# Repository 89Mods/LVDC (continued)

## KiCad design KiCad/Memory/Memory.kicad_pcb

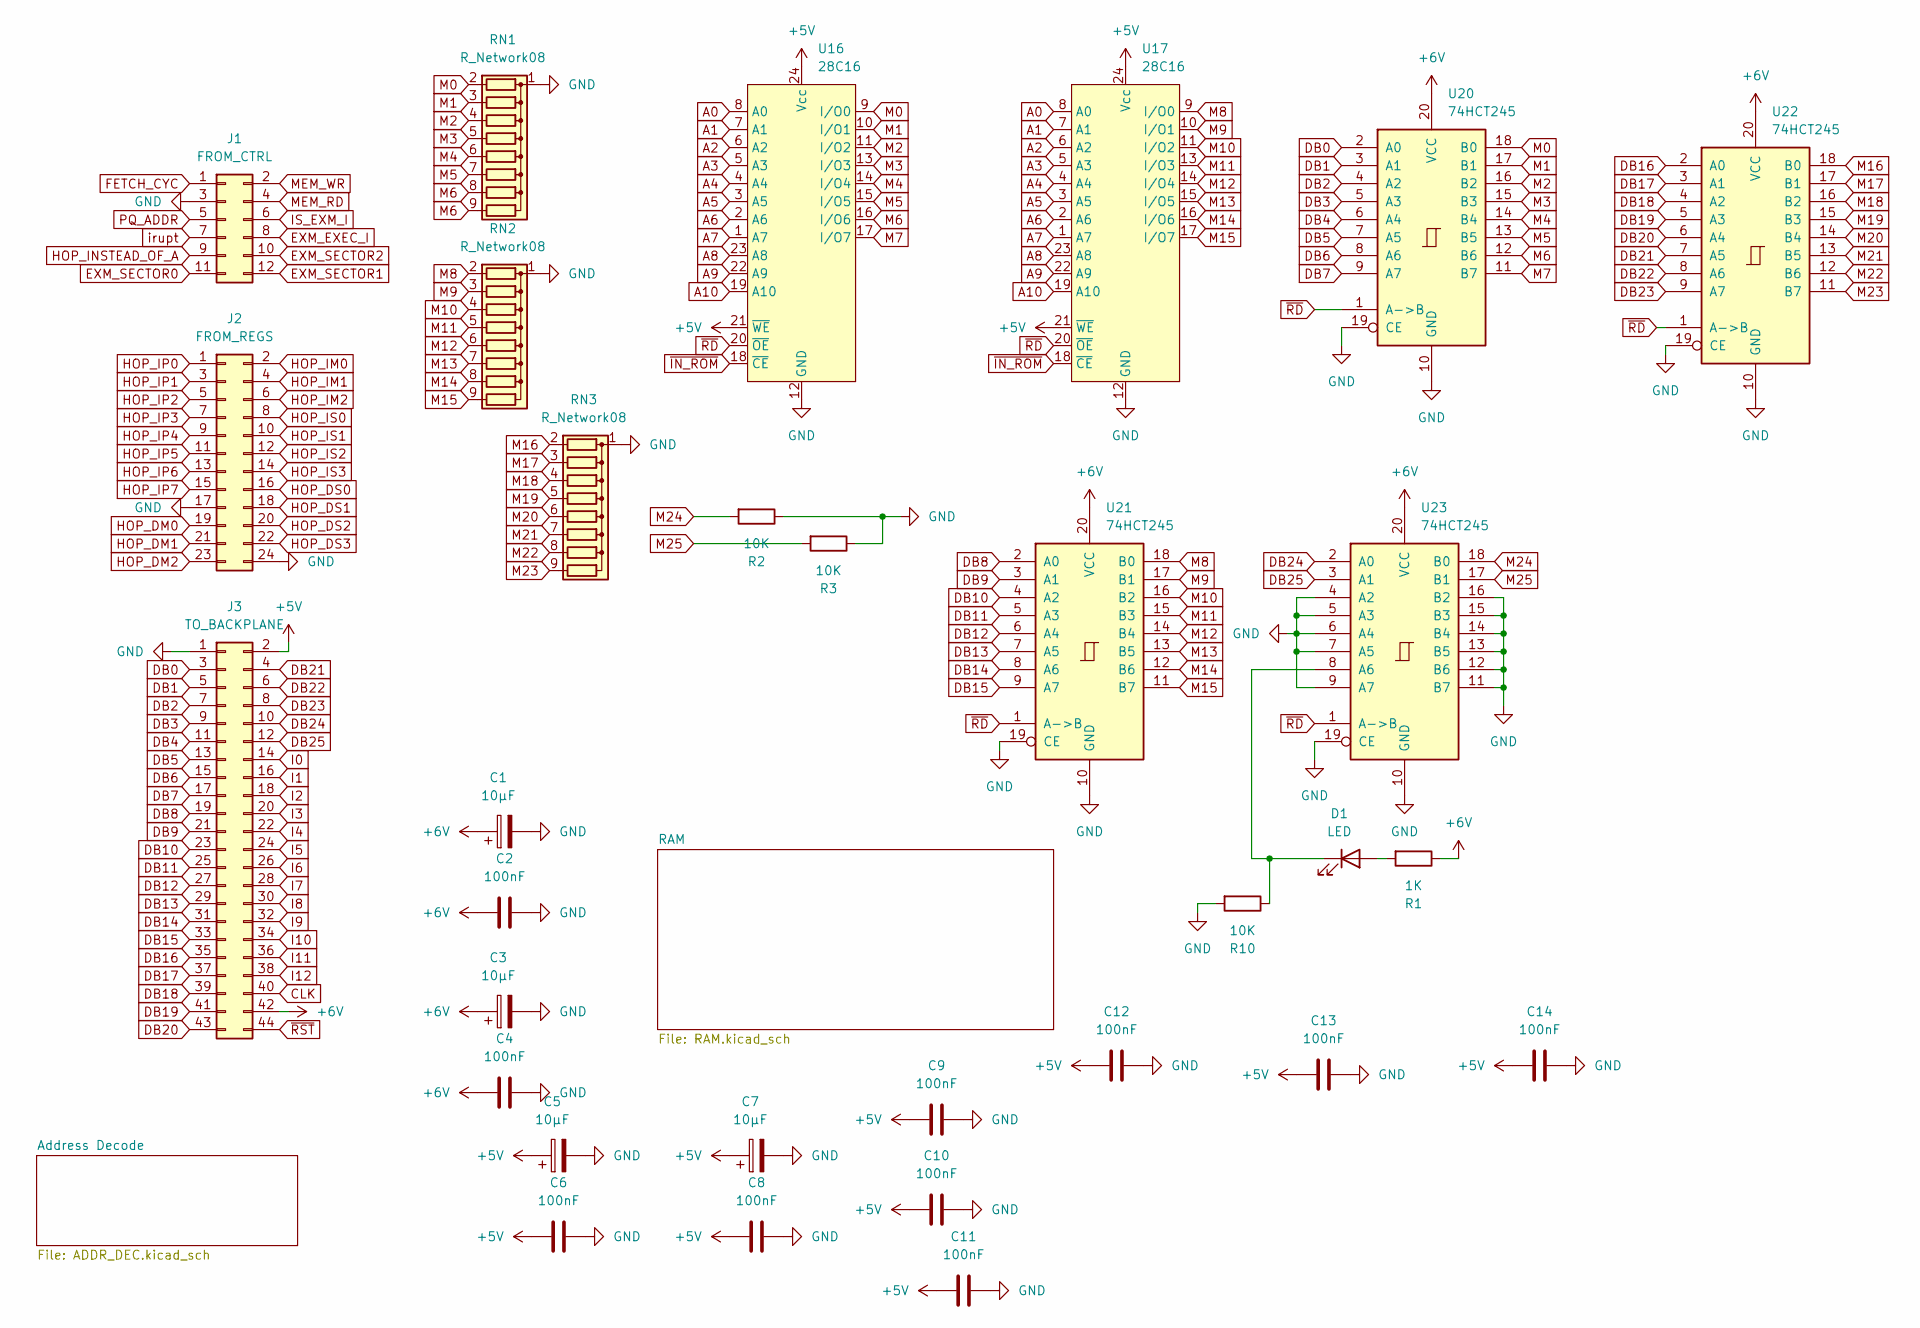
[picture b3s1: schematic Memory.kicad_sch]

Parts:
C1, C3, C5, C7: 10µF; CP_Radial_D4.0mm_P2.00mm
C2, C4, C6, C8, C9, C10, C11, C12, C13, C14: 100nF; C_0805_2012Metric_Pad1.18x1.45mm_HandSolder
D1: LED; LED_1206_3216Metric_Pad1.42x1.75mm_HandSolder
J1: FROM_CTRL; PinHeader_2x06_P2.54mm_Vertical
J2: FROM_REGS; PinHeader_2x12_P2.54mm_Vertical
J3: TO_BACKPLANE; PinHeader_2x22_P2.54mm_Vertical
R1: 1K; R_1206_3216Metric_Pad1.30x1.75mm_HandSolder
R2, R3, R10: 10K; R_1206_3216Metric_Pad1.30x1.75mm_HandSolder
RN1, RN2, RN3: R_Network08; R_Array_SIP9
U16, U17: 28C16; DIP-24_W15.24mm
U20, U21, U22, U23: 74HCT245; SO-20_12.8x7.5mm_P1.27mm

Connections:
+5V: C5.1, C6.1, C7.1, C8.1, C9.1, C10.1, C11.1, C12.1, C13.1, C14.1, J3.2, U16.21 (~WE), U16.24 (Vcc), U17.21 (~WE), U17.24 (Vcc); also elsewhere on the board
+6V: C1.1, C2.1, C3.1, C4.1, J3.42, R1.1, U20.20 (VCC), U21.20 (VCC), U22.20 (VCC), U23.20 (VCC)
A0: U16.8 (A0), U17.8 (A0); also elsewhere on the board
A1: U16.7 (A1), U17.7 (A1); also elsewhere on the board
A2: U16.6 (A2), U17.6 (A2); also elsewhere on the board
A3: U16.5 (A3), U17.5 (A3); also elsewhere on the board
A4: U16.4 (A4), U17.4 (A4); also elsewhere on the board
A5: U16.3 (A5), U17.3 (A5); also elsewhere on the board
A6: U16.2 (A6), U17.2 (A6); also elsewhere on the board
A7: U16.1 (A7), U17.1 (A7); also elsewhere on the board
A8: U16.23 (A8), U17.23 (A8); also elsewhere on the board
A9: U16.22 (A9), U17.22 (A9); also elsewhere on the board
A10: U16.19 (A10), U17.19 (A10); also elsewhere on the board
CLK: J3.40
DB0: J3.3, U20.2 (A0)
DB1: J3.5, U20.3 (A1)
DB2: J3.7, U20.4 (A2)
DB3: J3.9, U20.5 (A3)
DB4: J3.11, U20.6 (A4)
DB5: J3.13, U20.7 (A5)
DB6: J3.15, U20.8 (A6)
DB7: J3.17, U20.9 (A7)
DB8: J3.19, U21.2 (A0)
DB9: J3.21, U21.3 (A1)
DB10: J3.23, U21.4 (A2)
DB11: J3.25, U21.5 (A3)
DB12: J3.27, U21.6 (A4)
DB13: J3.29, U21.7 (A5)
DB14: J3.31, U21.8 (A6)
DB15: J3.33, U21.9 (A7)
DB16: J3.35, U22.2 (A0)
DB17: J3.37, U22.3 (A1)
DB18: J3.39, U22.4 (A2)
DB19: J3.41, U22.5 (A3)
DB20: J3.43, U22.6 (A4)
DB21: J3.4, U22.7 (A5)
DB22: J3.6, U22.8 (A6)
DB23: J3.8, U22.9 (A7)
DB24: J3.10, U23.2 (A0)
DB25: J3.12, U23.3 (A1)
EXM_EXEC_I: J1.8; also elsewhere on the board
EXM_SECTOR0: J1.11; also elsewhere on the board
EXM_SECTOR1: J1.12; also elsewhere on the board
EXM_SECTOR2: J1.10; also elsewhere on the board
FETCH_CYC: J1.1; also elsewhere on the board
GND: C1.2, C2.2, C3.2, C4.2, C5.2, C6.2, C7.2, C8.2, C9.2, C10.2, C11.2, C12.2, C13.2, C14.2, J1.3, J2.17, J2.24, J3.1, R2.1, R3.1, R10.2, RN1.1 (common), RN2.1 (common), RN3.1 (common), U16.12 (GND), U17.12 (GND), U20.10 (GND), U20.19 (CE), U21.10 (GND), U21.19 (CE), U22.10 (GND), U22.19 (CE), U23.4 (A2), U23.5 (A3), U23.6 (A4), U23.7 (A5), U23.9 (A7), U23.10 (GND), U23.11 (B7), U23.12 (B6), U23.13 (B5), U23.14 (B4), U23.15 (B3), U23.16 (B2), U23.19 (CE); also elsewhere on the board
HOP_DM0: J2.19; also elsewhere on the board
HOP_DM1: J2.21; also elsewhere on the board
HOP_DM2: J2.23; also elsewhere on the board
HOP_DS0: J2.16; also elsewhere on the board
HOP_DS1: J2.18; also elsewhere on the board
HOP_DS2: J2.20; also elsewhere on the board
HOP_DS3: J2.22; also elsewhere on the board
HOP_IM0: J2.2; also elsewhere on the board
HOP_IM1: J2.4; also elsewhere on the board
HOP_IM2: J2.6; also elsewhere on the board
HOP_INSTEAD_OF_A: J1.9; also elsewhere on the board
HOP_IP0: J2.1; also elsewhere on the board
HOP_IP1: J2.3; also elsewhere on the board
HOP_IP2: J2.5; also elsewhere on the board
HOP_IP3: J2.7; also elsewhere on the board
HOP_IP4: J2.9; also elsewhere on the board
HOP_IP5: J2.11; also elsewhere on the board
HOP_IP6: J2.13; also elsewhere on the board
HOP_IP7: J2.15; also elsewhere on the board
HOP_IS0: J2.8; also elsewhere on the board
HOP_IS1: J2.10; also elsewhere on the board
HOP_IS2: J2.12; also elsewhere on the board
HOP_IS3: J2.14; also elsewhere on the board
I0: J3.14
I1: J3.16
I2: J3.18
I3: J3.20
I4: J3.22; also elsewhere on the board
I5: J3.24; also elsewhere on the board
I6: J3.26; also elsewhere on the board
I7: J3.28; also elsewhere on the board
I8: J3.30; also elsewhere on the board
I9: J3.32; also elsewhere on the board
I10: J3.34; also elsewhere on the board
I11: J3.36; also elsewhere on the board
I12: J3.38; also elsewhere on the board
IS_EXM_I: J1.6; also elsewhere on the board
M0: RN1.2 (R1), U16.9 (I/O0), U20.18 (B0); also elsewhere on the board
M1: RN1.3 (R2), U16.10 (I/O1), U20.17 (B1); also elsewhere on the board
M2: RN1.4 (R3), U16.11 (I/O2), U20.16 (B2); also elsewhere on the board
M3: RN1.5 (R4), U16.13 (I/O3), U20.15 (B3); also elsewhere on the board
M4: RN1.6 (R5), U16.14 (I/O4), U20.14 (B4); also elsewhere on the board
M5: RN1.7 (R6), U16.15 (I/O5), U20.13 (B5); also elsewhere on the board
M6: RN1.8 (R7), RN1.9 (R8), U16.16 (I/O6), U20.12 (B6); also elsewhere on the board
M7: U16.17 (I/O7), U20.11 (B7); also elsewhere on the board
M8: RN2.2 (R1), U17.9 (I/O0), U21.18 (B0); also elsewhere on the board
M9: RN2.3 (R2), U17.10 (I/O1), U21.17 (B1); also elsewhere on the board
M10: RN2.4 (R3), U17.11 (I/O2), U21.16 (B2); also elsewhere on the board
M11: RN2.5 (R4), U17.13 (I/O3), U21.15 (B3); also elsewhere on the board
M12: RN2.6 (R5), U17.14 (I/O4), U21.14 (B4); also elsewhere on the board
M13: RN2.7 (R6), U17.15 (I/O5), U21.13 (B5); also elsewhere on the board
M14: RN2.8 (R7), U17.16 (I/O6), U21.12 (B6); also elsewhere on the board
M15: RN2.9 (R8), U17.17 (I/O7), U21.11 (B7); also elsewhere on the board
M16: RN3.2 (R1), U22.18 (B0); also elsewhere on the board
M17: RN3.3 (R2), U22.17 (B1); also elsewhere on the board
M18: RN3.4 (R3), U22.16 (B2); also elsewhere on the board
M19: RN3.5 (R4), U22.15 (B3); also elsewhere on the board
M20: RN3.6 (R5), U22.14 (B4); also elsewhere on the board
M21: RN3.7 (R6), U22.13 (B5); also elsewhere on the board
M22: RN3.8 (R7), U22.12 (B6); also elsewhere on the board
M23: RN3.9 (R8), U22.11 (B7); also elsewhere on the board
M24: R2.2, U23.18 (B0); also elsewhere on the board
M25: R3.2, U23.17 (B1); also elsewhere on the board
MEM_RD: J1.4; also elsewhere on the board
MEM_WR: J1.2; also elsewhere on the board
unnamed: D1.2 (A), R1.2
unnamed: D1.1 (K), R10.1, U23.8 (A6)
PQ_ADDR: J1.5; also elsewhere on the board
irupt: J1.7; also elsewhere on the board
~IN_ROM: U16.18 (~CE), U17.18 (~CE); also elsewhere on the board
~RD: U16.20 (~OE), U17.20 (~OE), U20.1 (A->B), U21.1 (A->B), U22.1 (A->B), U23.1 (A->B); also elsewhere on the board
~RST: J3.44

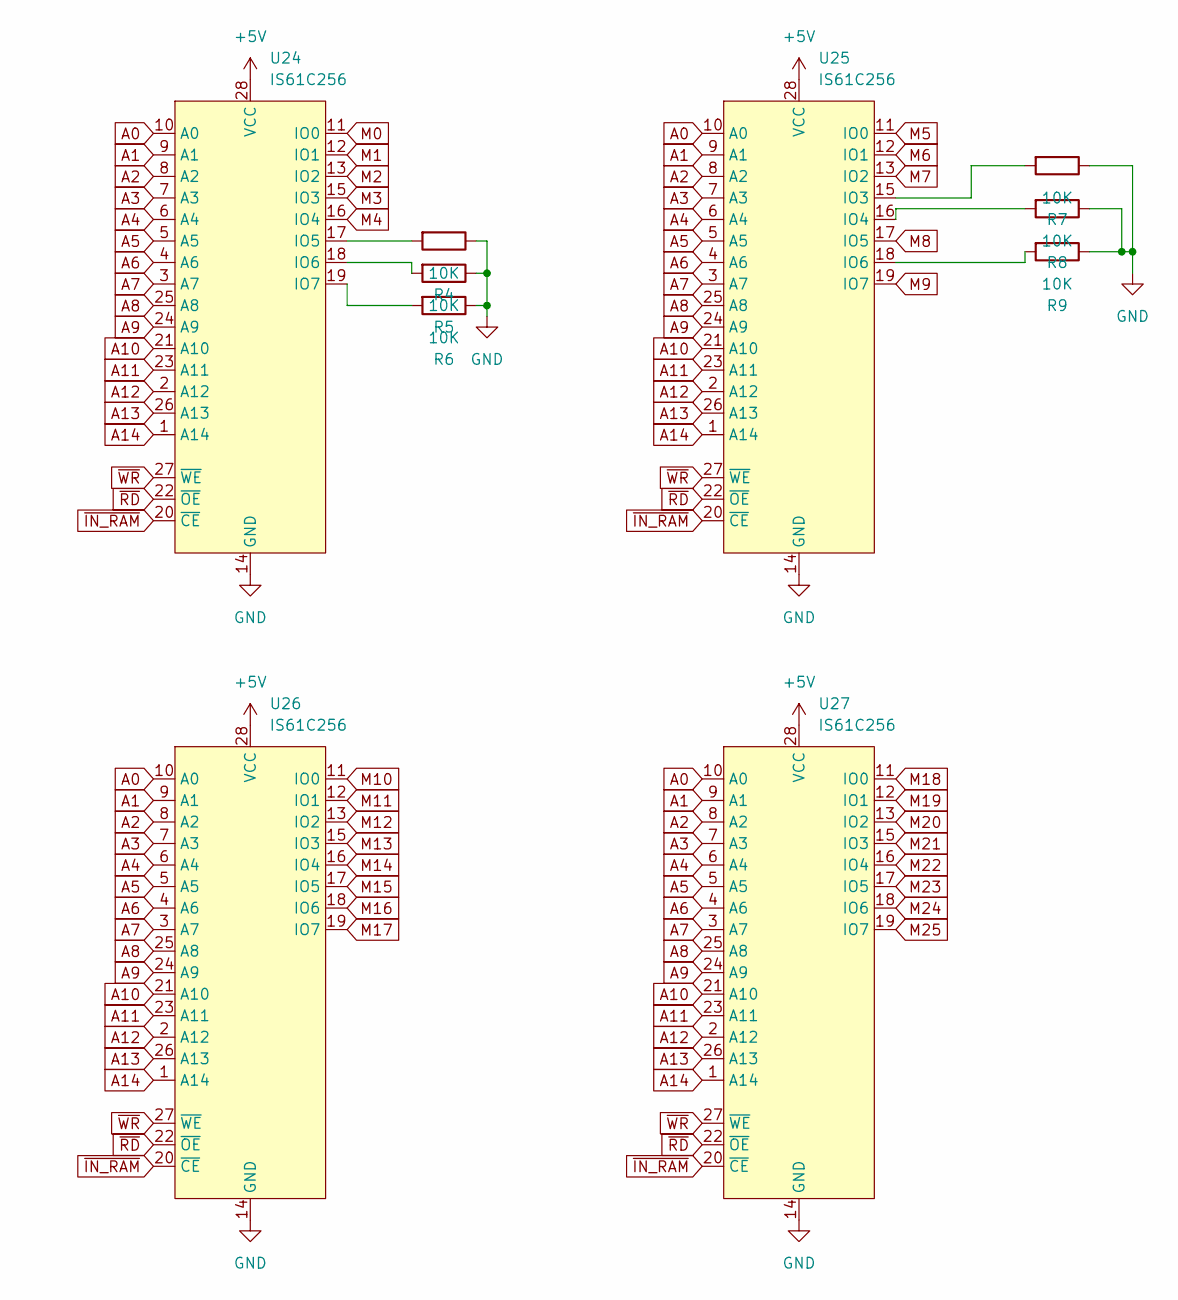
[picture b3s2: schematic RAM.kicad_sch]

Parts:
R4, R5, R6, R7, R8, R9: 10K; R_1206_3216Metric_Pad1.30x1.75mm_HandSolder
U24, U25, U26, U27: IS61C256; DIP-28_W7.62mm

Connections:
+5V: U24.28 (VCC), U25.28 (VCC), U26.28 (VCC), U27.28 (VCC); also elsewhere on the board
A0: U24.10 (A0), U25.10 (A0), U26.10 (A0), U27.10 (A0); also elsewhere on the board
A1: U24.9 (A1), U25.9 (A1), U26.9 (A1), U27.9 (A1); also elsewhere on the board
A2: U24.8 (A2), U25.8 (A2), U26.8 (A2), U27.8 (A2); also elsewhere on the board
A3: U24.7 (A3), U25.7 (A3), U26.7 (A3), U27.7 (A3); also elsewhere on the board
A4: U24.6 (A4), U25.6 (A4), U26.6 (A4), U27.6 (A4); also elsewhere on the board
A5: U24.5 (A5), U25.5 (A5), U26.5 (A5), U27.5 (A5); also elsewhere on the board
A6: U24.4 (A6), U25.4 (A6), U26.4 (A6), U27.4 (A6); also elsewhere on the board
A7: U24.3 (A7), U25.3 (A7), U26.3 (A7), U27.3 (A7); also elsewhere on the board
A8: U24.25 (A8), U25.25 (A8), U26.25 (A8), U27.25 (A8); also elsewhere on the board
A9: U24.24 (A9), U25.24 (A9), U26.24 (A9), U27.24 (A9); also elsewhere on the board
A10: U24.21 (A10), U25.21 (A10), U26.21 (A10), U27.21 (A10); also elsewhere on the board
A11: U24.23 (A11), U25.23 (A11), U26.23 (A11), U27.23 (A11); also elsewhere on the board
A12: U24.2 (A12), U25.2 (A12), U26.2 (A12), U27.2 (A12); also elsewhere on the board
A13: U24.26 (A13), U25.26 (A13), U26.26 (A13), U27.26 (A13); also elsewhere on the board
A14: U24.1 (A14), U25.1 (A14), U26.1 (A14), U27.1 (A14); also elsewhere on the board
GND: R4.1, R5.1, R6.1, R7.1, R8.1, R9.1, U24.14 (GND), U25.14 (GND), U26.14 (GND), U27.14 (GND); also elsewhere on the board
M0: U24.11 (IO0); also elsewhere on the board
M1: U24.12 (IO1); also elsewhere on the board
M2: U24.13 (IO2); also elsewhere on the board
M3: U24.15 (IO3); also elsewhere on the board
M4: U24.16 (IO4); also elsewhere on the board
M5: U25.11 (IO0); also elsewhere on the board
M6: U25.12 (IO1); also elsewhere on the board
M7: U25.13 (IO2); also elsewhere on the board
M8: U25.17 (IO5); also elsewhere on the board
M9: U25.19 (IO7); also elsewhere on the board
M10: U26.11 (IO0); also elsewhere on the board
M11: U26.12 (IO1); also elsewhere on the board
M12: U26.13 (IO2); also elsewhere on the board
M13: U26.15 (IO3); also elsewhere on the board
M14: U26.16 (IO4); also elsewhere on the board
M15: U26.17 (IO5); also elsewhere on the board
M16: U26.18 (IO6); also elsewhere on the board
M17: U26.19 (IO7); also elsewhere on the board
M18: U27.11 (IO0); also elsewhere on the board
M19: U27.12 (IO1); also elsewhere on the board
M20: U27.13 (IO2); also elsewhere on the board
M21: U27.15 (IO3); also elsewhere on the board
M22: U27.16 (IO4); also elsewhere on the board
M23: U27.17 (IO5); also elsewhere on the board
M24: U27.18 (IO6); also elsewhere on the board
M25: U27.19 (IO7); also elsewhere on the board
unnamed: R4.2, U24.17 (IO5)
unnamed: R5.2, U24.18 (IO6)
unnamed: R6.2, U24.19 (IO7)
unnamed: R7.2, U25.15 (IO3)
unnamed: R8.2, U25.16 (IO4)
unnamed: R9.2, U25.18 (IO6)
~IN_RAM: U24.20 (~CE), U25.20 (~CE), U26.20 (~CE), U27.20 (~CE); also elsewhere on the board
~RD: U24.22 (~OE), U25.22 (~OE), U26.22 (~OE), U27.22 (~OE); also elsewhere on the board
~WR: U24.27 (~WE), U25.27 (~WE), U26.27 (~WE), U27.27 (~WE); also elsewhere on the board

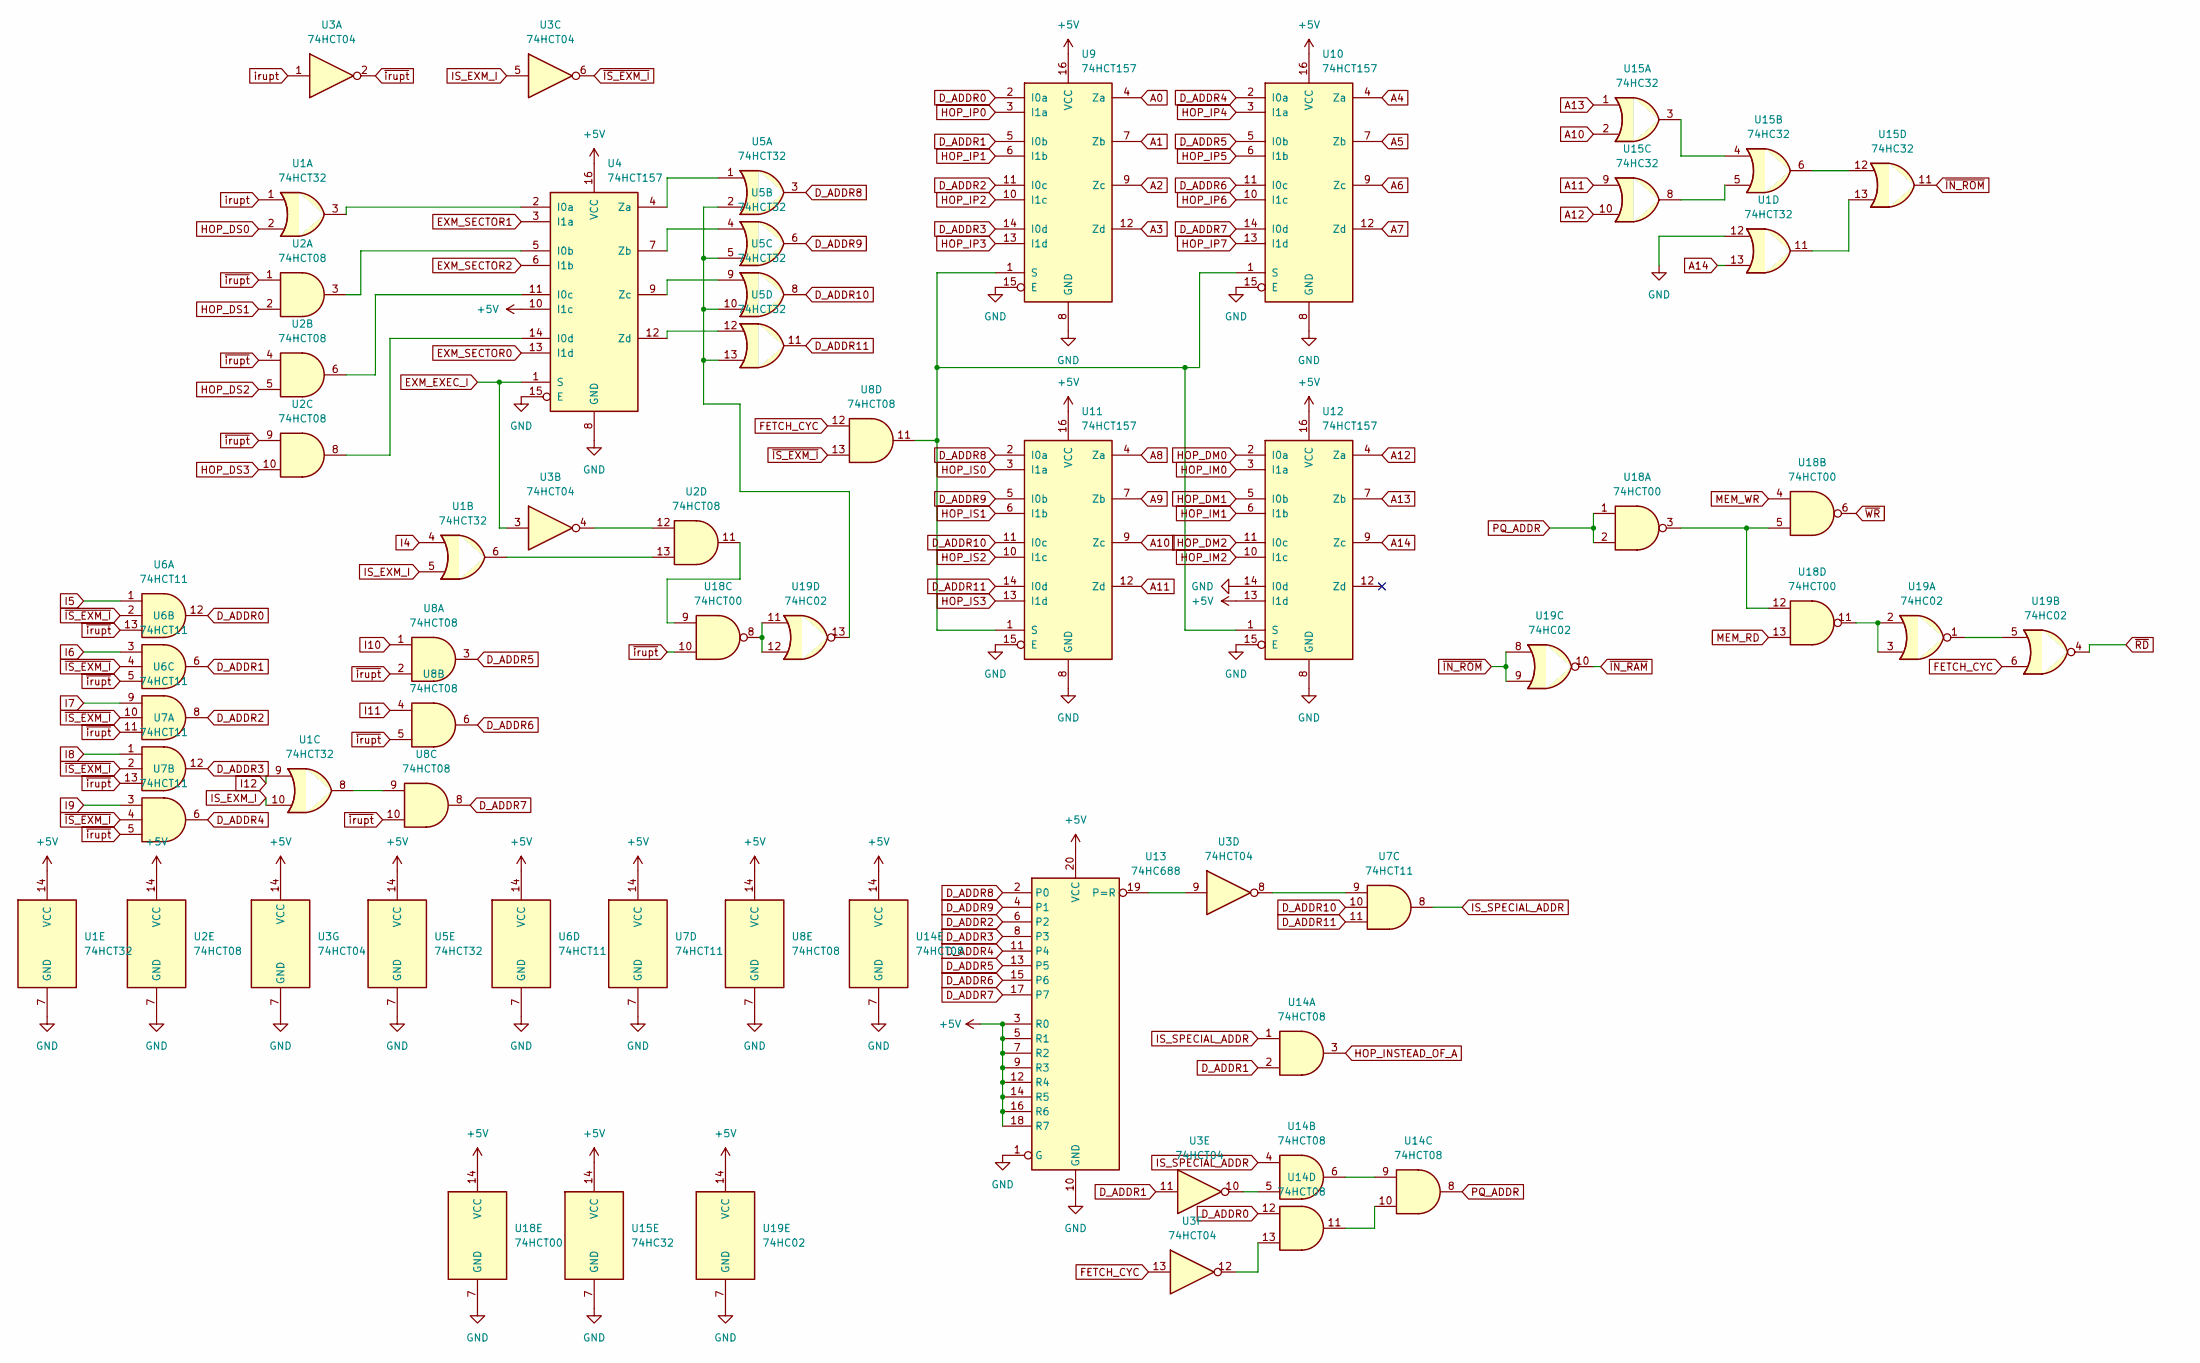
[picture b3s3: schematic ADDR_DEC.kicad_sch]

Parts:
U1, U5: 74HCT32; SO-14_3.9x8.65mm_P1.27mm
U2, U8, U14: 74HCT08; SO-14_3.9x8.65mm_P1.27mm
U3: 74HCT04; SO-14_3.9x8.65mm_P1.27mm
U4, U9, U10, U11, U12: 74HCT157; SO-16_3.9x9.9mm_P1.27mm
U6, U7: 74HCT11; SO-14_3.9x8.65mm_P1.27mm
U13: 74HC688; SO-20_12.8x7.5mm_P1.27mm
U15: 74HC32; SO-14_3.9x8.65mm_P1.27mm
U18: 74HCT00; SO-14_3.9x8.65mm_P1.27mm
U19: 74HC02; SO-14_3.9x8.65mm_P1.27mm

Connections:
+5V: U1.14 (VCC), U2.14 (VCC), U3.14 (VCC), U4.10 (I1c), U4.16 (VCC), U5.14 (VCC), U6.14 (VCC), U7.14 (VCC), U8.14 (VCC), U9.16 (VCC), U10.16 (VCC), U11.16 (VCC), U12.13 (I1d), U12.16 (VCC), U13.3 (R0), U13.5 (R1), U13.7 (R2), U13.9 (R3), U13.12 (R4), U13.14 (R5), U13.16 (R6), U13.18 (R7), U13.20 (VCC), U14.14 (VCC), U15.14 (VCC), U18.14 (VCC), U19.14 (VCC); also elsewhere on the board
A0: U9.4 (Za); also elsewhere on the board
A1: U9.7 (Zb); also elsewhere on the board
A2: U9.9 (Zc); also elsewhere on the board
A3: U9.12 (Zd); also elsewhere on the board
A4: U10.4 (Za); also elsewhere on the board
A5: U10.7 (Zb); also elsewhere on the board
A6: U10.9 (Zc); also elsewhere on the board
A7: U10.12 (Zd); also elsewhere on the board
A8: U11.4 (Za); also elsewhere on the board
A9: U11.7 (Zb); also elsewhere on the board
A10: U11.9 (Zc), U15.2; also elsewhere on the board
A11: U11.12 (Zd), U15.9; also elsewhere on the board
A12: U12.4 (Za), U15.10; also elsewhere on the board
A13: U12.7 (Zb), U15.1; also elsewhere on the board
A14: U1.13, U12.9 (Zc); also elsewhere on the board
D_ADDR0: U6.12, U9.2 (I0a), U14.12
D_ADDR1: U3.11, U6.6, U9.5 (I0b), U14.2
D_ADDR2: U6.8, U9.11 (I0c), U13.6 (P2)
D_ADDR3: U7.12, U9.14 (I0d), U13.8 (P3)
D_ADDR4: U7.6, U10.2 (I0a), U13.11 (P4)
D_ADDR5: U8.3, U10.5 (I0b), U13.13 (P5)
D_ADDR6: U8.6, U10.11 (I0c), U13.15 (P6)
D_ADDR7: U8.8, U10.14 (I0d), U13.17 (P7)
D_ADDR8: U5.3, U11.2 (I0a), U13.2 (P0)
D_ADDR9: U5.6, U11.5 (I0b), U13.4 (P1)
D_ADDR10: U5.8, U7.10, U11.11 (I0c)
D_ADDR11: U5.11, U7.11, U11.14 (I0d)
EXM_EXEC_I: U3.3, U4.1 (S); also elsewhere on the board
EXM_SECTOR0: U4.13 (I1d); also elsewhere on the board
EXM_SECTOR1: U4.3 (I1a); also elsewhere on the board
EXM_SECTOR2: U4.6 (I1b); also elsewhere on the board
FETCH_CYC: U3.13, U8.12, U19.6; also elsewhere on the board
GND: U1.7 (GND), U1.12, U2.7 (GND), U3.7 (GND), U4.8 (GND), U4.15 (E), U5.7 (GND), U6.7 (GND), U7.7 (GND), U8.7 (GND), U9.8 (GND), U9.15 (E), U10.8 (GND), U10.15 (E), U11.8 (GND), U11.15 (E), U12.8 (GND), U12.14 (I0d), U12.15 (E), U13.1 (G), U13.10 (GND), U14.7 (GND), U15.7 (GND), U18.7 (GND), U19.7 (GND); also elsewhere on the board
HOP_DM0: U12.2 (I0a); also elsewhere on the board
HOP_DM1: U12.5 (I0b); also elsewhere on the board
HOP_DM2: U12.11 (I0c); also elsewhere on the board
HOP_DS0: U1.2; also elsewhere on the board
HOP_DS1: U2.2; also elsewhere on the board
HOP_DS2: U2.5; also elsewhere on the board
HOP_DS3: U2.10; also elsewhere on the board
HOP_IM0: U12.3 (I1a); also elsewhere on the board
HOP_IM1: U12.6 (I1b); also elsewhere on the board
HOP_IM2: U12.10 (I1c); also elsewhere on the board
HOP_INSTEAD_OF_A: U14.3; also elsewhere on the board
HOP_IP0: U9.3 (I1a); also elsewhere on the board
HOP_IP1: U9.6 (I1b); also elsewhere on the board
HOP_IP2: U9.10 (I1c); also elsewhere on the board
HOP_IP3: U9.13 (I1d); also elsewhere on the board
HOP_IP4: U10.3 (I1a); also elsewhere on the board
HOP_IP5: U10.6 (I1b); also elsewhere on the board
HOP_IP6: U10.10 (I1c); also elsewhere on the board
HOP_IP7: U10.13 (I1d); also elsewhere on the board
HOP_IS0: U11.3 (I1a); also elsewhere on the board
HOP_IS1: U11.6 (I1b); also elsewhere on the board
HOP_IS2: U11.10 (I1c); also elsewhere on the board
HOP_IS3: U11.13 (I1d); also elsewhere on the board
I4: U1.4; also elsewhere on the board
I5: U6.1; also elsewhere on the board
I6: U6.3; also elsewhere on the board
I7: U6.9; also elsewhere on the board
I8: U7.1; also elsewhere on the board
I9: U7.3; also elsewhere on the board
I10: U8.1; also elsewhere on the board
I11: U8.4; also elsewhere on the board
I12: U1.9; also elsewhere on the board
IS_EXM_I: U1.5, U1.10, U3.5; also elsewhere on the board
IS_SPECIAL_ADDR: U7.8, U14.1, U14.4
MEM_RD: U18.13; also elsewhere on the board
MEM_WR: U18.4; also elsewhere on the board
unnamed: U1.6, U2.13
unnamed: U1.8, U8.9
unnamed: U1.11, U15.13
unnamed: U2.12, U3.4
unnamed: U3.8, U7.9
unnamed: U1.3, U4.2 (I0a)
unnamed: U2.3, U4.5 (I0b)
unnamed: U2.6, U4.11 (I0c)
unnamed: U2.8, U4.14 (I0d)
unnamed: U4.4 (Za), U5.1
unnamed: U4.7 (Zb), U5.4
unnamed: U4.9 (Zc), U5.9
unnamed: U4.12 (Zd), U5.12
unnamed: U8.11, U9.1 (S), U10.1 (S), U11.1 (S), U12.1 (S)
unnamed: U3.9, U13.19 (P=R)
unnamed: U3.10, U14.5
unnamed: U14.6, U14.9
unnamed: U14.10, U14.11
unnamed: U3.12, U14.13
unnamed: U15.3, U15.4
unnamed: U15.5, U15.8
unnamed: U15.6, U15.12
unnamed: U18.8, U19.11, U19.12
unnamed: U2.11, U18.9
unnamed: U18.11, U19.2, U19.3
unnamed: U18.3, U18.5, U18.12
unnamed: U19.1, U19.5
unnamed: U5.2, U5.5, U5.10, U5.13, U19.13
PQ_ADDR: U14.8, U18.1, U18.2; also elsewhere on the board
irupt: U1.1, U3.1; also elsewhere on the board
~IN_RAM: U19.10; also elsewhere on the board
~IN_ROM: U15.11, U19.8, U19.9; also elsewhere on the board
~IS_EXM_I: U3.6, U6.2, U6.4, U6.10, U7.2, U7.4, U8.13
~RD: U19.4; also elsewhere on the board
~WR: U18.6; also elsewhere on the board
~irupt: U2.1, U2.4, U2.9, U3.2, U6.5, U6.11, U6.13, U7.5, U7.13, U8.2, U8.5, U8.10, U18.10

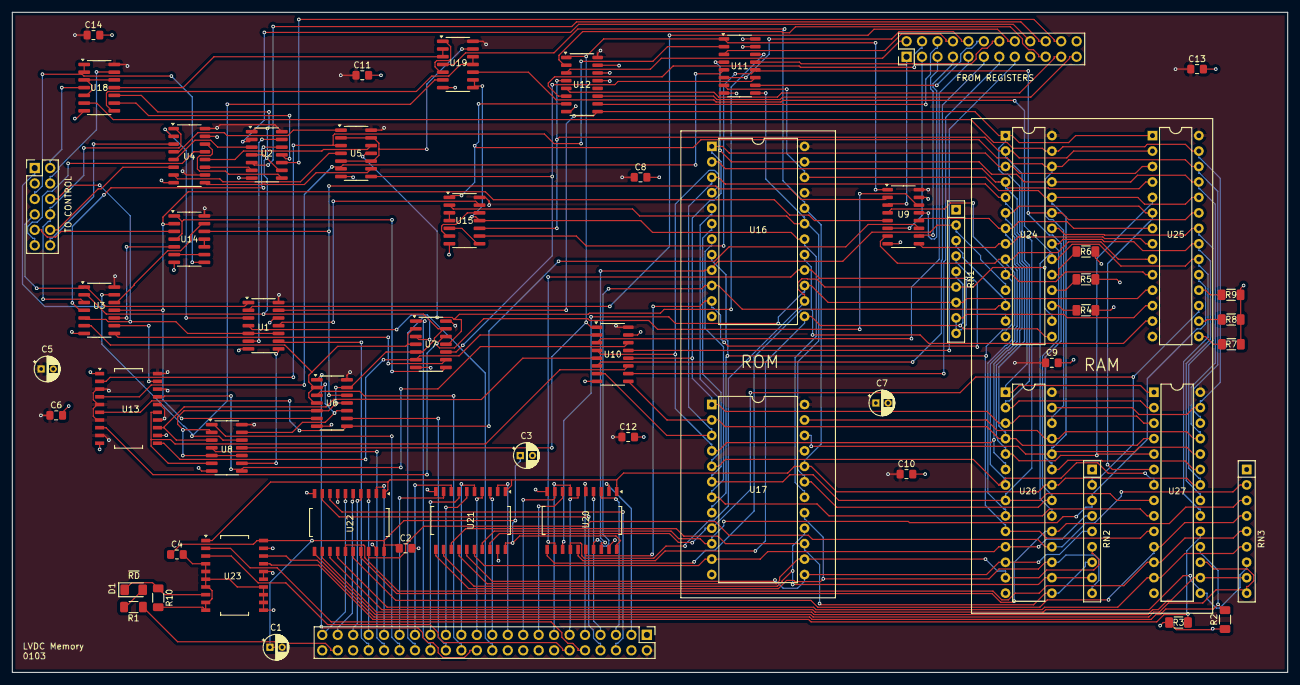
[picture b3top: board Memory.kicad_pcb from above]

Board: 4 copper layers, 209.5 x 108.5 mm, 58 parts (0 on the bottom side), 167 nets.

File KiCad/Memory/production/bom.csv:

Designator,Footprint,Quantity,Value,LCSC Part #
"C1, C3, C5, C7",CP_Radial_D4.0mm_P2.00mm,4,10µF,
"C10, C11, C12, C13, C14, C2, C4, C6, C8, C9",0805,10,100nF,
D1,1206,1,LED,
J1,PinHeader_2x06_P2.54mm_Vertical,1,FROM_CTRL,
J2,PinHeader_2x12_P2.54mm_Vertical,1,FROM_REGS,
J3,PinHeader_2x22_P2.54mm_Vertical,1,TO_BACKPLANE,
R1,1206,1,1K,
"R10, R2, R3, R4, R5, R6, R7, R8, R9",1206,9,10K,
"RN1, RN2, RN3",R_Array_SIP9,3,R_Network08,
"U1, U5",SO-14_3.9x8.65mm_P1.27mm,2,74HCT32,
"U10, U11, U12, U4, U9",SO-16_3.9x9.9mm_P1.27mm,5,74HCT157,
U13,SO-20_12.8x7.5mm_P1.27mm,1,74HC688,
"U14, U2, U8",SO-14_3.9x8.65mm_P1.27mm,3,74HCT08,
U15,SO-14_3.9x8.65mm_P1.27mm,1,74HC32,
"U16, U17",DIP-24_W15.24mm,2,28C16,
U18,SO-14_3.9x8.65mm_P1.27mm,1,74HCT00,
U19,SO-14_3.9x8.65mm_P1.27mm,1,74HC02,
"U20, U21, U22, U23",SO-20_12.8x7.5mm_P1.27mm,4,74HCT245,
"U24, U25, U26, U27",DIP-28_W7.62mm,4,IS61C256,
U3,SO-14_3.9x8.65mm_P1.27mm,1,74HCT04,
"U6, U7",SO-14_3.9x8.65mm_P1.27mm,2,74HCT11,

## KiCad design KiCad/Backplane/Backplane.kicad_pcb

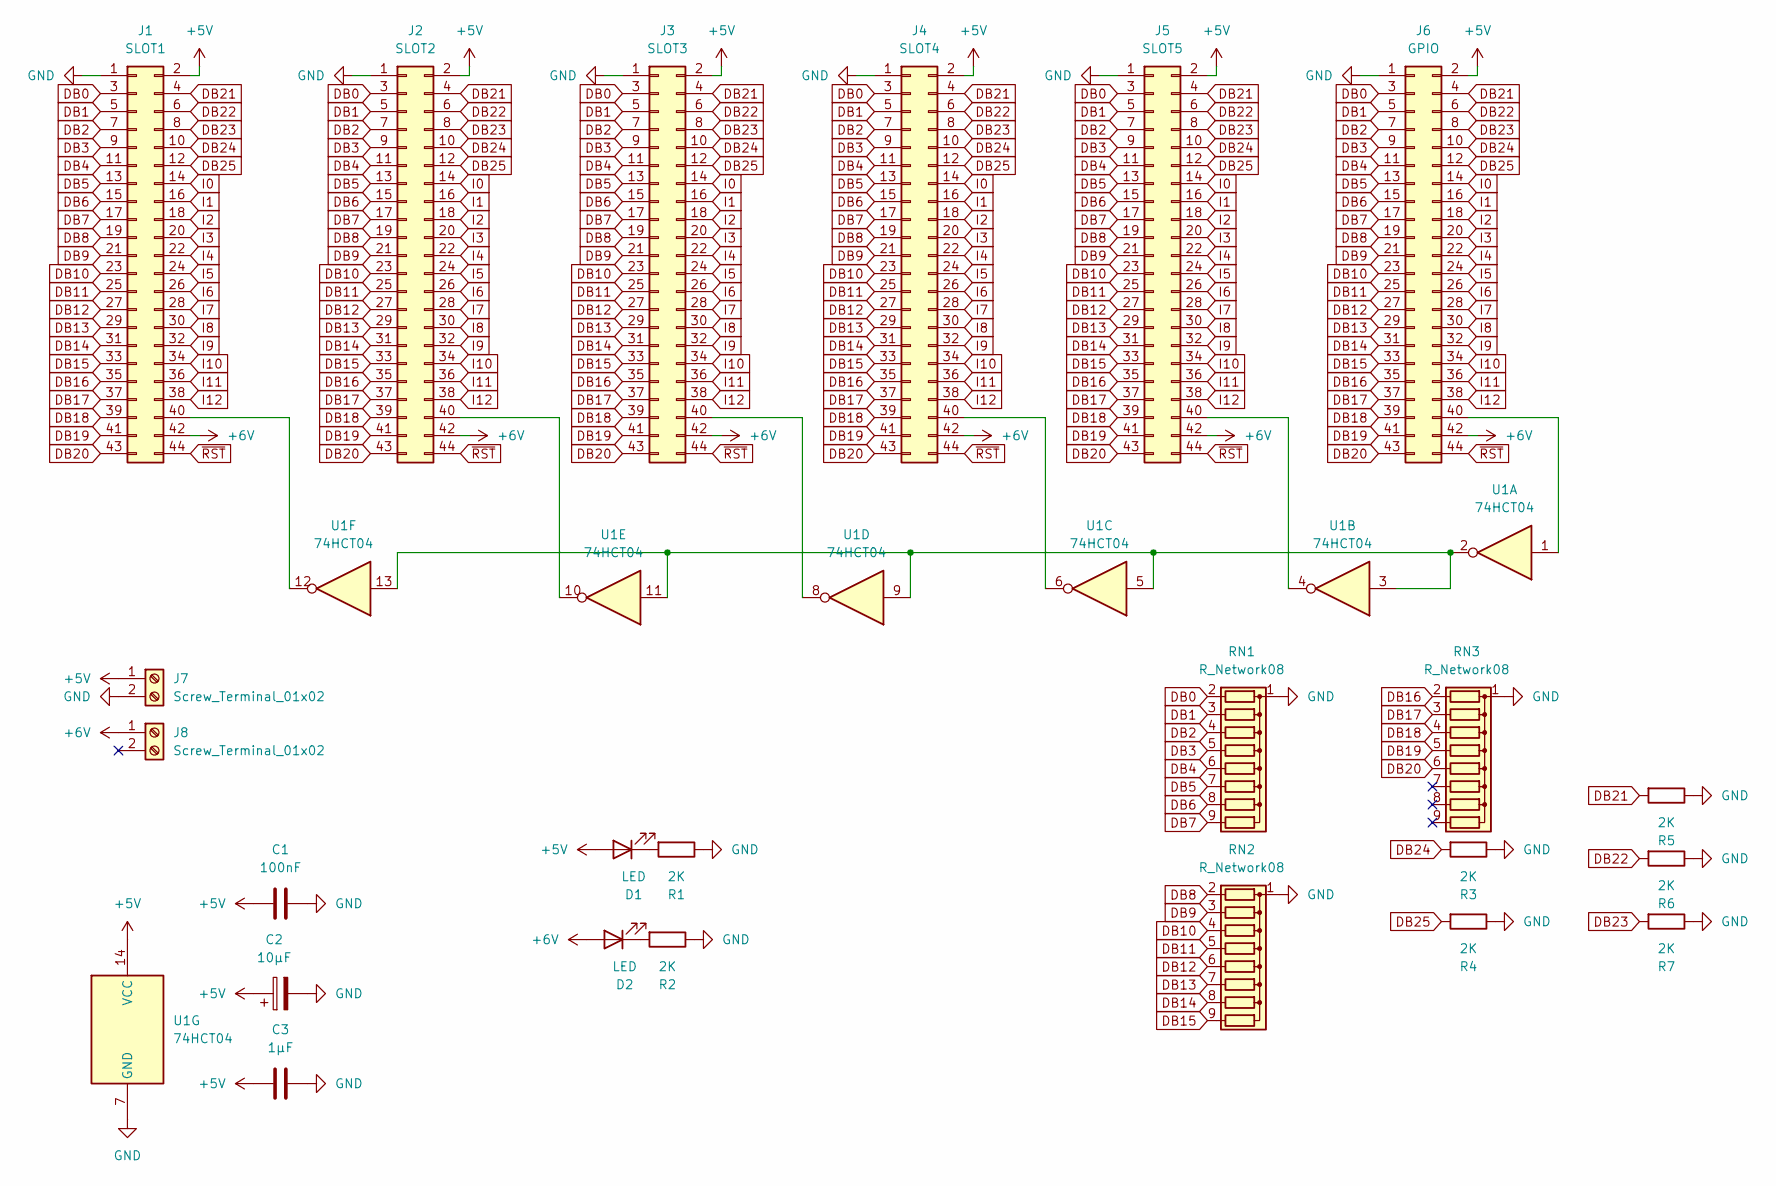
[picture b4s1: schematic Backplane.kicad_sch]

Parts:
C1: 100nF; C_0805_2012Metric_Pad1.18x1.45mm_HandSolder
C2: 10µF; CP_Radial_D4.0mm_P2.00mm
C3: 1µF; C_0805_2012Metric_Pad1.18x1.45mm_HandSolder
D1, D2: LED; LED_1206_3216Metric_Pad1.42x1.75mm_HandSolder
J1: SLOT1; PinHeader_2x22_P2.54mm_Vertical
J2: SLOT2; PinHeader_2x22_P2.54mm_Vertical
J3: SLOT3; PinHeader_2x22_P2.54mm_Vertical
J4: SLOT4; PinHeader_2x22_P2.54mm_Vertical
J5: SLOT5; PinHeader_2x22_P2.54mm_Vertical
J6: GPIO; PinHeader_2x22_P2.54mm_Vertical
J7, J8: Screw_Terminal_01x02; TerminalBlock_bornier-2_P5.08mm
R1, R2, R3, R4, R5, R6, R7: 2K; R_1206_3216Metric_Pad1.30x1.75mm_HandSolder
RN1, RN2, RN3: R_Network08; R_Array_SIP9
U1: 74HCT04; DIP-14_W7.62mm

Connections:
+5V: C1.1, C2.1, C3.1, D1.2 (A), J1.2, J2.2, J3.2, J4.2, J5.2, J6.2, J7.1, U1.14 (VCC)
+6V: D2.2 (A), J1.42, J2.42, J3.42, J4.42, J5.42, J6.42, J8.1
DB0: J1.3, J2.3, J3.3, J4.3, J5.3, J6.3, RN1.2 (R1)
DB1: J1.5, J2.5, J3.5, J4.5, J5.5, J6.5, RN1.3 (R2)
DB2: J1.7, J2.7, J3.7, J4.7, J5.7, J6.7, RN1.4 (R3)
DB3: J1.9, J2.9, J3.9, J4.9, J5.9, J6.9, RN1.5 (R4)
DB4: J1.11, J2.11, J3.11, J4.11, J5.11, J6.11, RN1.6 (R5)
DB5: J1.13, J2.13, J3.13, J4.13, J5.13, J6.13, RN1.7 (R6)
DB6: J1.15, J2.15, J3.15, J4.15, J5.15, J6.15, RN1.8 (R7)
DB7: J1.17, J2.17, J3.17, J4.17, J5.17, J6.17, RN1.9 (R8)
DB8: J1.19, J2.19, J3.19, J4.19, J5.19, J6.19, RN2.2 (R1)
DB9: J1.21, J2.21, J3.21, J4.21, J5.21, J6.21, RN2.3 (R2)
DB10: J1.23, J2.23, J3.23, J4.23, J5.23, J6.23, RN2.4 (R3)
DB11: J1.25, J2.25, J3.25, J4.25, J5.25, J6.25, RN2.5 (R4)
DB12: J1.27, J2.27, J3.27, J4.27, J5.27, J6.27, RN2.6 (R5)
DB13: J1.29, J2.29, J3.29, J4.29, J5.29, J6.29, RN2.7 (R6)
DB14: J1.31, J2.31, J3.31, J4.31, J5.31, J6.31, RN2.8 (R7)
DB15: J1.33, J2.33, J3.33, J4.33, J5.33, J6.33, RN2.9 (R8)
DB16: J1.35, J2.35, J3.35, J4.35, J5.35, J6.35, RN3.2 (R1)
DB17: J1.37, J2.37, J3.37, J4.37, J5.37, J6.37, RN3.3 (R2)
DB18: J1.39, J2.39, J3.39, J4.39, J5.39, J6.39, RN3.4 (R3)
DB19: J1.41, J2.41, J3.41, J4.41, J5.41, J6.41, RN3.5 (R4)
DB20: J1.43, J2.43, J3.43, J4.43, J5.43, J6.43, RN3.6 (R5)
DB21: J1.4, J2.4, J3.4, J4.4, J5.4, J6.4, R5.2
DB22: J1.6, J2.6, J3.6, J4.6, J5.6, J6.6, R6.2
DB23: J1.8, J2.8, J3.8, J4.8, J5.8, J6.8, R7.2
DB24: J1.10, J2.10, J3.10, J4.10, J5.10, J6.10, R3.2
DB25: J1.12, J2.12, J3.12, J4.12, J5.12, J6.12, R4.2
GND: C1.2, C2.2, C3.2, J1.1, J2.1, J3.1, J4.1, J5.1, J6.1, J7.2, R1.1, R2.1, R3.1, R4.1, R5.1, R6.1, R7.1, RN1.1 (common), RN2.1 (common), RN3.1 (common), U1.7 (GND)
I0: J1.14, J2.14, J3.14, J4.14, J5.14, J6.14
I1: J1.16, J2.16, J3.16, J4.16, J5.16, J6.16
I2: J1.18, J2.18, J3.18, J4.18, J5.18, J6.18
I3: J1.20, J2.20, J3.20, J4.20, J5.20, J6.20
I4: J1.22, J2.22, J3.22, J4.22, J5.22, J6.22
I5: J1.24, J2.24, J3.24, J4.24, J5.24, J6.24
I6: J1.26, J2.26, J3.26, J4.26, J5.26, J6.26
I7: J1.28, J2.28, J3.28, J4.28, J5.28, J6.28
I8: J1.30, J2.30, J3.30, J4.30, J5.30, J6.30
I9: J1.32, J2.32, J3.32, J4.32, J5.32, J6.32
I10: J1.34, J2.34, J3.34, J4.34, J5.34, J6.34
I11: J1.36, J2.36, J3.36, J4.36, J5.36, J6.36
I12: J1.38, J2.38, J3.38, J4.38, J5.38, J6.38
unnamed: D1.1 (K), R1.2
unnamed: D2.1 (K), R2.2
unnamed: J1.40, U1.12
unnamed: J2.40, U1.10
unnamed: J3.40, U1.8
unnamed: J4.40, U1.6
unnamed: J5.40, U1.4
unnamed: J6.40, U1.1
unnamed: U1.2, U1.3, U1.5, U1.9, U1.11, U1.13
~RST: J1.44, J2.44, J3.44, J4.44, J5.44, J6.44
